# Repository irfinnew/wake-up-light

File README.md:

# About

This is a dawn simulation lamp I made for my personal use.

A dawn simulator wakes you up by simulating sunrise in the bedroom; the increasing amount of light starts preparing your body for awakening.
The end result is that you naturally wake up on your own, instead of being jarred awake by the usual alarm clock sounds.

When it receives power, the wake-up light

 - Very gently increases from darkness to full brightness over the course of 30 minutes,
 - Remains at full brightness for 45 minutes,
 - Then turns off fairly quickly.

The wake-up light is switched on by a plug-in timer that activates 45 minutes before my intended rise time.

It also includes a button to toggle the light between off and full brightness, so I can turn it off after I get up.

# Design

The light controller is a classic [phase-cutting](https://en.wikipedia.org/wiki/Phase-fired_controller) triac dimmer, with zero-cross detection and triac control performed by a small microcontroller.
The dimmer drives a 150W halogen floodlight, which gives a nice orange glow at low brightness, but provides reasonably white full-spectrum light at high brightness.

The design was also a bit of an engineering exercise; I wanted to end up with a fairly minimal design without compromising stability or reliability.

## Isolation

The controller is not isolated from mains; it uses a capacitive dropper power supply, and the MCU is connected directly to the triac.
As a result, the entire circuit may be at mains potential, it must be installed so that users can't touch any of it.
This also applies to the button, which must provide adequate isolation.

The MCU also connects directly to mains for zero-cross sensing, as inspired by [Atmel application note AN2508](https://ww1.microchip.com/downloads/en/Appnotes/Atmel-2508-Zero-Cross-Detector_ApplicationNote_AVR182.pdf).

## Mains voltage and frequency

The controller was designed to run on 230VAC @ 50Hz.
If you want to run it on 120VAC, the power supply caps (`C1/C2`) probably should be doubled in value.
The firmware should be able to deal with 60Hz without problems, but I haven't tested this.

# Sources

The PCB layout is provided as a [KiCad](https://www.kicad.org/) project in `pcb/`.
The project uses a handful of custom footprints in `pcb/WakeUpLight.pretty/`, you'll need to import them into KiCad.

Gerber files in `pcb/gerber/`.

## Firmware

The firmware for the ATTiny45P lives in `mcu/`.
It is written in C, for `avr-gcc` / `avr-libc`.
If you have a `stk500v1` compatible programmer on USB and `avrdude`, just `SERIAL=/dev/ttyUSB0 make upload` should do the trick.

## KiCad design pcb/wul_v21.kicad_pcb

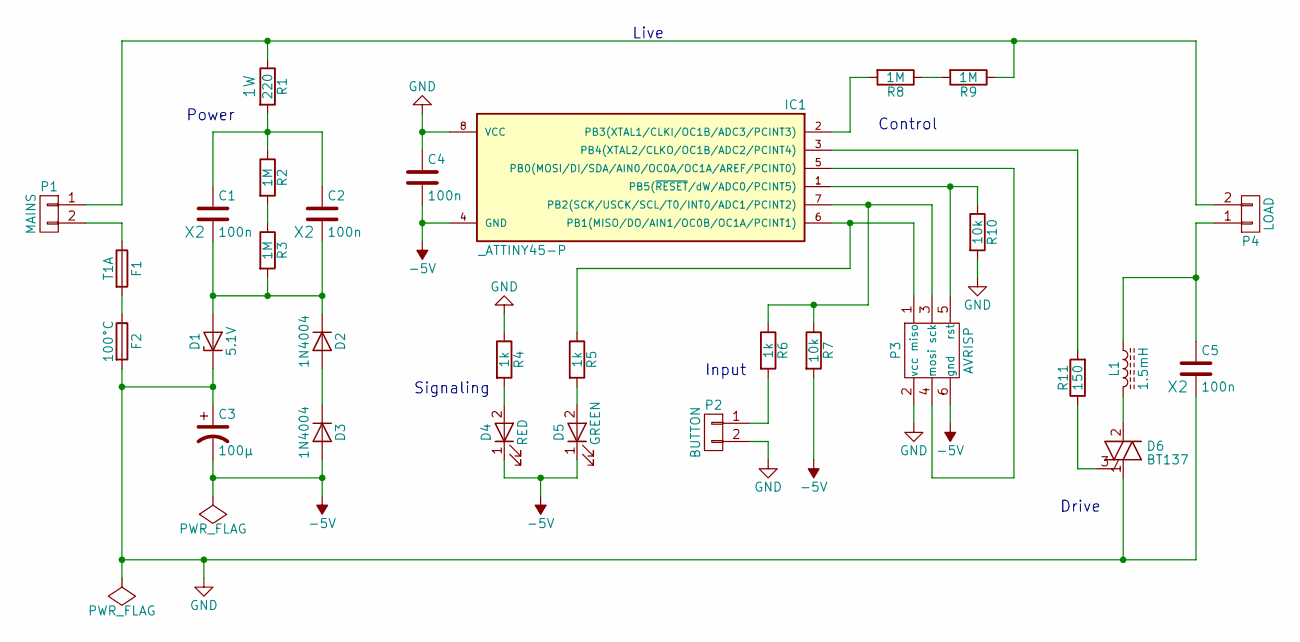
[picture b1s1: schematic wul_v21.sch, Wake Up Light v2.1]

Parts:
C1, C2, C5: 100n; C_Rect_L18_W6_H12_P15; Rating X2
C3: 100µ; C_Radial_D8_L13_P3.8
C4: 100n; C_Disc_D6_P5
D1: 5.1V; Diode_DO-35_SOD27_Horizontal_RM10
D2, D3: 1N4004; Diode_DO-41_SOD81_Horizontal_RM10
D4: RED; LED-3MM
D5: GREEN; LED-3MM
D6: BT137; TO-220_Wide
F1: T1A; Fuseholder5x20_horiz_open_inline_Type-I
F2: 100°C; C_Rect_L13_W4_P10
IC1: _ATTINY45-P; DIP-8_W7.62mm
L1: 1.5mH; Choke_Toroid_15x36mm_Vertical
P1: MAINS; bornier2_wide
P2: BUTTON; Pin_Header_Straight_1x02
P3: AVRISP; Pin_Header_Straight_2x03
P4: LOAD; bornier2_wide
R1: 220; Resistor_Horizontal_RM15mm; Rating 1W
R2, R3: 1M; Resistor_Horizontal_RM7mm
R4, R5, R6: 1k; Resistor_Horizontal_RM10mm
R7, R10: 10k; Resistor_Horizontal_RM10mm
R8, R9: 1M; Resistor_Horizontal_RM10mm
R11: 150; Resistor_Horizontal_RM10mm

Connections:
-5V: C3.2, C4.2, D3.2 (A), D4.1 (K), D5.1 (K), IC1.4 (GND), P3.6 (gnd), R7.2
GND: C3.1, C4.1, C5.2, D1.1 (K), D6.1 (A2), F2.2, IC1.8 (VCC), P2.2, P3.2 (vcc), R4.1, R10.2
unnamed: C1.1, C2.1, R1.2, R2.1
unnamed: C1.2, C2.2, D1.2 (A), D2.1 (K), R3.2
unnamed: C5.1, L1.1, P4.1
unnamed: D2.2 (A), D3.1 (K)
unnamed: D4.2 (A), R4.2
unnamed: D5.2 (A), R5.2
unnamed: D6.2 (A1), L1.2
unnamed: D6.3 (G), R11.1
unnamed: F1.1, P1.2
unnamed: F1.2, F2.1
unnamed: IC1.1 (PB5(~RESET~/dW/ADC0/PCINT5)), P3.5 (rst), R10.1
unnamed: IC1.2 (PB3(XTAL1/CLKI/OC1B/ADC3/PCINT3)), R8.2
unnamed: IC1.3 (PB4(XTAL2/CLKO/OC1B/ADC2/PCINT4)), R11.2
unnamed: IC1.5 (PB0(MOSI/DI/SDA/AIN0/OC0A/OC1A/AREF/PCI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), P3.4 (mosi)
unnamed: IC1.6 (PB1(MISO/DO/AIN1/OC0B/OC1A/PCINT1)), P3.1 (miso), R5.1
unnamed: IC1.7 (PB2(SCK/USCK/SCL/T0/INT0/ADC1/PCINT2)), P3.3 (sck), R6.1, R7.1
unnamed: P1.1, P4.2, R1.1, R9.1
unnamed: P2.1, R6.2
unnamed: R2.2, R3.1
unnamed: R8.1, R9.2

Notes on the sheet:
Power
Drive
Signaling
Input
Control
Live

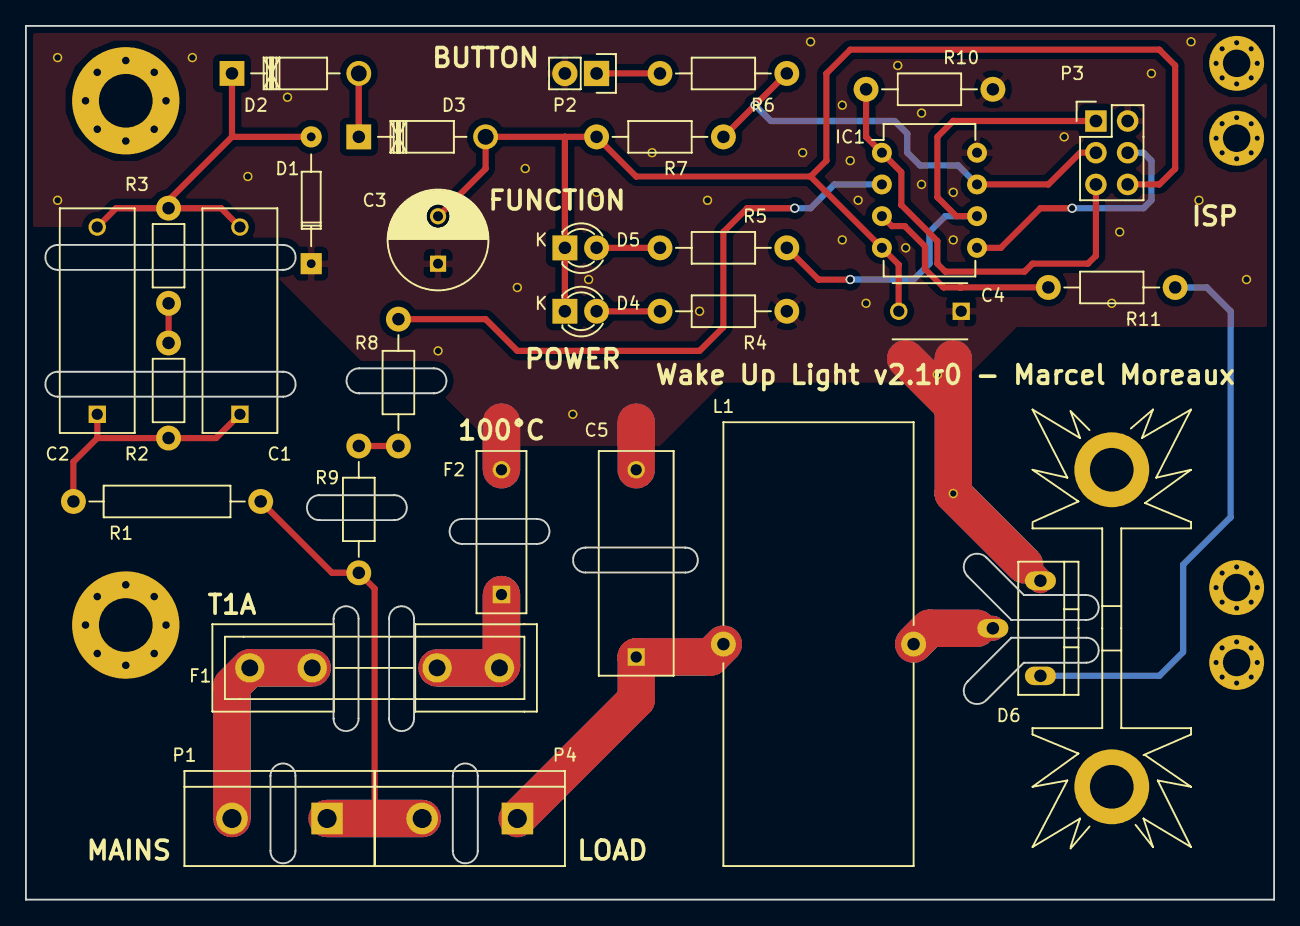
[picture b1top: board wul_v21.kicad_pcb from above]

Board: 2 copper layers, 100.0 x 70.0 mm, 30 parts (0 on the bottom side), 22 nets.

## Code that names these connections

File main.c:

#define F_CPU (2*1000000UL)

#include <avr/io.h>
#include <util/delay.h>

#define US_PULSE 100
#define LVL_MAX 0x7fffffff
#define LVL_SCALE(x) ((x >> 16) << 1)
#define LVL_RAMP(x) (LVL_MAX / 100 / x)

#define PIN_ZEROCROSS PB3
#define PIN_LED       PB1
#define PIN_BUTTON    PB2
#define PIN_TRIAC     PB4



// Fast 16x16 -> high16 multiplication approximation.
// Equivalent to (a * b) >> 16  (ignoring overflow)
//
// XXX: this function is an approximation. In 25% of the cases, the 
// return value is 1 lower than it should be. Never higher.
//
// Cycle count on GCC 4.8.1 with -Os: 166 + (# of bits set in <a>)
// (add 7 for call/ret)
unsigned int mul16_h16(unsigned int a, unsigned int b)
{
	unsigned int c = 0;
	unsigned char i;

	b >>= 1;
	for (i = 0; i < 16; i++)
	{
		c >>= 1;
		if (a & 0x01)
			c += b;
		a >>= 1;
	}
	return c;
}



// Blinks the led. Call once every semicycle. The parameters indicate
// how many semicycles the led should be on, and how many off (254 MAX).
// E.g. blink(50, 50) is 0.5 sec on, 0.5 sec off (assuming 50Hz)
// blink(10, 90) is 0.1 sec on, 0.9 off. etc.
void blink(unsigned char on, unsigned char off)
{
	static unsigned char state = 0;
	static unsigned char count = 0;

	count++;

	if (state == 0 && count > off && on > 0)
	{
		PORTB |= _BV(PIN_LED);
		state = 1;
		count = 0;
		return;
	}

	if (state == 1 && count > on && off > 0)
	{
		PORTB &= ~_BV(PIN_LED);
		state = 0;
		count = 0;
		return;
	}
}



// Returns true iff the button is pressed and was depressed the previous 7
// invocations of this function. If polled every semicycle, this provides
// good debouncing.
unsigned char button_pressed(void)
{
	static unsigned char acc = 0;

	acc <<= 1;
	if (PINB & _BV(PIN_BUTTON))
		acc |= 1;

	return acc == 0x01;
}



// They "main loop" function, which waits out the rest of the semicycle,
// triggering the triac at an appropriate moment (as indicated by level).
// Call this function, do a little processing, call it again, etc, etc.
// Try to keep time between calls as constant as possible.
// Level indicates brightness, ranging from 0 to 0xffff.
// Actual resolution appears to be something like 1 in 1500.
void cycle(unsigned int level)
{
	// Keep track of which semicycle we're dealing with.
	// 0xff for the lower semicycle, 0x00 for the upper half.
	static unsigned char which = 0x00;
	// The mains cycle length in loop counts. About 1500-ish.
	static unsigned int cycle_len = 0xffff;
	// Loop counter for the current iteration.
	unsigned int count = 0;
	// Target loop counts after which to trigger the triac.
	unsigned int target = 0;



	// Implement a level scaling that starts out linear but
	// tends to hypercubed eventually. This is a lot closer to
	// perceived linear brightness due to the way incandescents
	// and AC sine waves interact. (abuses target as temp var)
	target = mul16_h16(level, level);
	target = mul16_h16(target, target);
	target = (target >> 1) + (level >> 1);

	// Invert level; a low level translates to a high target
	target = 0xffffU - target;
	// We pretend the cycle is 128 counts shorter than it really is, to
	// prevent overshoot. About 0x40 seems really needed to prevent
	// incorrect triac triggering. The larger value makes level=0 close to
	// the glow point of the halogens I use.
	target = mul16_h16(cycle_len - 0x90, target);

	// At lowest level, set an unreachable target to ensure the triac
	// never gets fired. (count seems to run up to 1500-ish)
	// The expensive target calculation is discarded in this case, but we
	// want the computations to always happen to avoid runtime variations.
	if (level == 0)
		target = 0xffffU;



	// Because of the way this zero-cross detection works, the upper
	// semicycle appears longer by about 1%.  We compensate for this by
	// delaying for a bit before the main loop of the lower semicycle.
	// This ensures <count> is roughly the same for both semis.
	// 63us empirically found to be most stable.
	if (!which)
		_delay_us(63);



	count = 0;
	// Bitwise I/O accumulator, for debouncing.
	unsigned char io_acc = ~which;
	// Copy of <which> in a non-static variable. Otherwise GCC fails to
	// realize it doesn't have to fetch <which> from SRAM every iteration.
	unsigned char io_tgt = which;
	// Actual phase timing loop starts here.
	while (io_acc != io_tgt)
	{
		io_acc <<= 1;
		if (PINB & _BV(PIN_ZEROCROSS))
			io_acc |= 1;

		if (count == target)
		{
			PORTB &= ~_BV(PIN_TRIAC);
			_delay_us(US_PULSE);
			PORTB |= _BV(PIN_TRIAC);
			// Count compensation because of pulse delay.
			// One count should be 13 cycles.
			// One pulse is 100us, or 200 cycles at 2 MHz.
			// So, compensate by 200 / 13 = 15.
			count += 15;
		}

		count++;
	}

	// Start-up hack.
	// <cycle_len> starts out at 0xffff. <count> will be 1500-ish, so
	// <cycle_len> gets decreased each iteration. After 4 iterations,
	// it reaches 0xfffb, triggering a one-time shortcut to <count>.
	if (cycle_len == 0xfffb)
		cycle_len = count;

	// Adjust cycle_len, if needed. Adjusting by one step max prevents
	// intererence from messing things up too badly.
	if (count > cycle_len)
		cycle_len++;
	if (count < cycle_len)
		cycle_len--;

	// Select the other semicycle.
	which = ~which;
}



int main (void)
{
	unsigned long level;

	// Set clock prescaler to 256, resulting in a ~32KHz clock.
	// This minimizes power consumption.
	CLKPR = 0x80;
	CLKPR = 0x08;

	// Wait a little. At minimal power consumption, this allows the power
	// supply to stabilize. At 1/64th clock, this actually delays ~64ms.
	_delay_ms(1);

	// Set clock prescaler to 4, resulting in a ~2MHz clock.
	// This is our actual working frequency.
	CLKPR = 0x80;
	CLKPR = 0x02;

	// Set outputs
	PORTB |= _BV(PIN_TRIAC); // High = inactive
	DDRB = _BV(PIN_TRIAC) | _BV(PIN_LED);

	// Synchronize to the AC sine wave.
	cycle(0);
	cycle(0);



	// Ramp up
	for (level = 0; level <= LVL_MAX; level += LVL_RAMP(1800))
	{
		cycle(LVL_SCALE(level));
		blink(5, 15);
		if (button_pressed())
			goto off;
	}

	// Steady
	for (level = 0; level <= LVL_MAX; level += LVL_RAMP(2700))
	{
		cycle(0xffffU);
		blink(1, 0);
		if (button_pressed())
		{
			level = LVL_MAX;
			goto off;
		}
	}

	// Ramp down
	for (level = LVL_MAX; level <= LVL_MAX; level -= LVL_RAMP(2))
	{
		cycle(LVL_SCALE(level));
		blink(15, 5);
	}

off:
	// Off
	for (; level <= LVL_MAX; level -= LVL_RAMP(0.5))
	{
		cycle(LVL_SCALE(level));
		blink(5, 5);
		if (button_pressed())
			goto on;
	}
	level = 0;
	for (;;)
	{
		cycle(0);
		blink(5, 95);
		if (button_pressed())
			goto on;
	}

on:
	// On (only reachable by button)
	for (; level <= LVL_MAX; level += LVL_RAMP(1))
	{
		cycle(LVL_SCALE(level));
		blink(5, 5);
		if (button_pressed())
			goto off;
	}
	level = LVL_MAX;
	for (;;)
	{
		cycle(0xffffU);
		blink(95, 5);
		if (button_pressed())
			goto off;
	}

}

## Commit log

2015-12-08 Initial checkin.
2015-12-08 Adjusted dimmer for Vcc-as-common operation.
2015-12-24 Added button support.
2015-12-24 Better button support.
2016-05-15 Updated Makefiles.
2016-07-31 Macro fixes + comment improvements.
2016-07-31 Added hex file.
2016-07-31 Makefile.
2019-04-27 Moved code into mcu/
2019-04-27 Added pcb/
2022-07-01 Added better layout and front render images.
2022-07-03 Added LICENSE
2022-07-04 Added README.md
2022-07-11 Added cover image to README
